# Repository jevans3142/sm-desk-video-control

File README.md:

# ADC Theatre - SM Desk Video Switcher

This repository hosts the hardware (in the form of KiCad schematics and PCB layouts) and 
firmware (in the form of C code) of the [ADC Theatre's](https://www.adctheatre.com) Stage 
Manager's Desk Video Switcher. This is a control panel within the SM desk on stage which 
provides remote control of a Blackmagic Design Videohub SDI switcher via Ethernet.

## Features
* Controls four screen outputs on the SM Desk, with six sources (which can differ for each of the screens) routable via 24 buttons on the desk
* Provides a special 'Show Relay' source which is switched between the Main and IR camera both on the SM Desk and around the building
* Is the interface for the Main/IR switch button the SM Desk, and also controls the mains contactor to activate the IR floodlights when in IR camera mode

## Configuration

Although some things such as number of buttons etc are fixed in hardware, some aspects can be customised via a text file 
on a microSD card read at boot. This provides the ADC with the ability to reconfigure for example which sources are availible on the SM desk without having to recompile firmware (as long as the physical buttons are relabeled of course!)

Items which can be configured: 
* Which router inputs are used as sources for each of the destinations 
* For the special 'Show Relay' source, which router inputs are the Main and IR camera 
* Which router outputs are used as 'Show Relay' outputs and should be automatically switched between Main and IR cameras in sync with the SM Desk
* IP address of the router

## Compilation
The microcontroller used is an ESP32 on an Olimex ESP32-PoE-ISO board. After standard installation of the esp-idf FreeRTOS toolchain, currently building on v5.1.1 as a stable version with the configuration included in the src folder (ie. when building do not run the idf.py set-target esp32 command as directed in the esp-idf Getting Started instructions to set up the default build config - just go straight to idf.py build)

## Hardware

There are two types of PCB required. Four 'switch-module' PCBs sit behind the four sets of buttons on the SM desk (four 
destinations with six sources each). One 'main-board' PCB is connected to these panel boards via ribbon cables, and also 
to Ethernet and power.

## Copyright
Copyright (c) 2021-2022 John Evans and contributors.
The ADC SM Desk Video Switcher hardware and firmware is released under Version 3 of the GNU General Public License.
See the LICENSE file for full details.

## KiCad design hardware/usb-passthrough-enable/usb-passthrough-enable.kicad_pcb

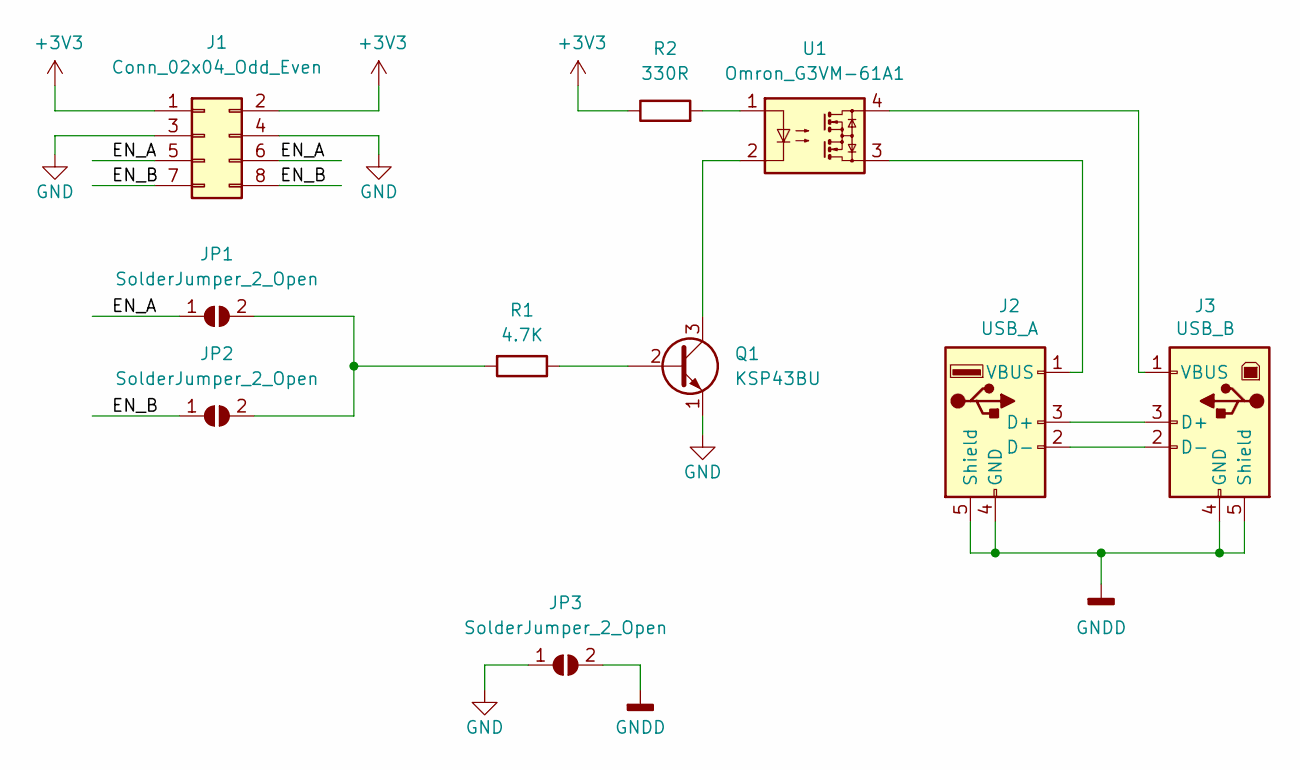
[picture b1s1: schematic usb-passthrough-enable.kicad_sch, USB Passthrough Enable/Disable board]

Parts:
J1: Conn_02x04_Odd_Even; PinHeader_2x04_P2.54mm_Vertical
J2: USB_A; USB_A_ASSMANN_A-USB-E-R
J3: USB_B; USB_B_ASSMANN_A-USBSB
JP1, JP2, JP3: SolderJumper_2_Open; SolderJumper-2_P1.3mm_Open_RoundedPad1.0x1.5mm
Q1: KSP43BU; TO-92_Inline
R1: 4.7K; R_Axial_DIN0207_L6.3mm_D2.5mm_P10.16mm_Horizontal
R2: 330R; R_Axial_DIN0207_L6.3mm_D2.5mm_P10.16mm_Horizontal
U1: Omron_G3VM-61A1; DIP-4_W7.62mm

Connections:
+3V3: J1.1, J1.2, R2.1
/EN_A: J1.5, J1.6, JP1.1 (A)
/EN_B: J1.7, J1.8, JP2.1 (A)
GND: J1.3, J1.4, JP3.1 (A), Q1.1 (E)
GNDD: J2.4 (GND), J2.5 (Shield), J3.4 (GND), J3.5 (Shield), JP3.2 (B)
unnamed: J2.3 (D+), J3.3 (D+)
unnamed: J2.2 (D-), J3.2 (D-)
unnamed: J2.1 (VBUS), U1.3
unnamed: J3.1 (VBUS), U1.4
unnamed: JP1.2 (B), JP2.2 (B), R1.2
unnamed: Q1.2 (B), R1.1
unnamed: Q1.3 (C), U1.2
unnamed: R2.2, U1.1

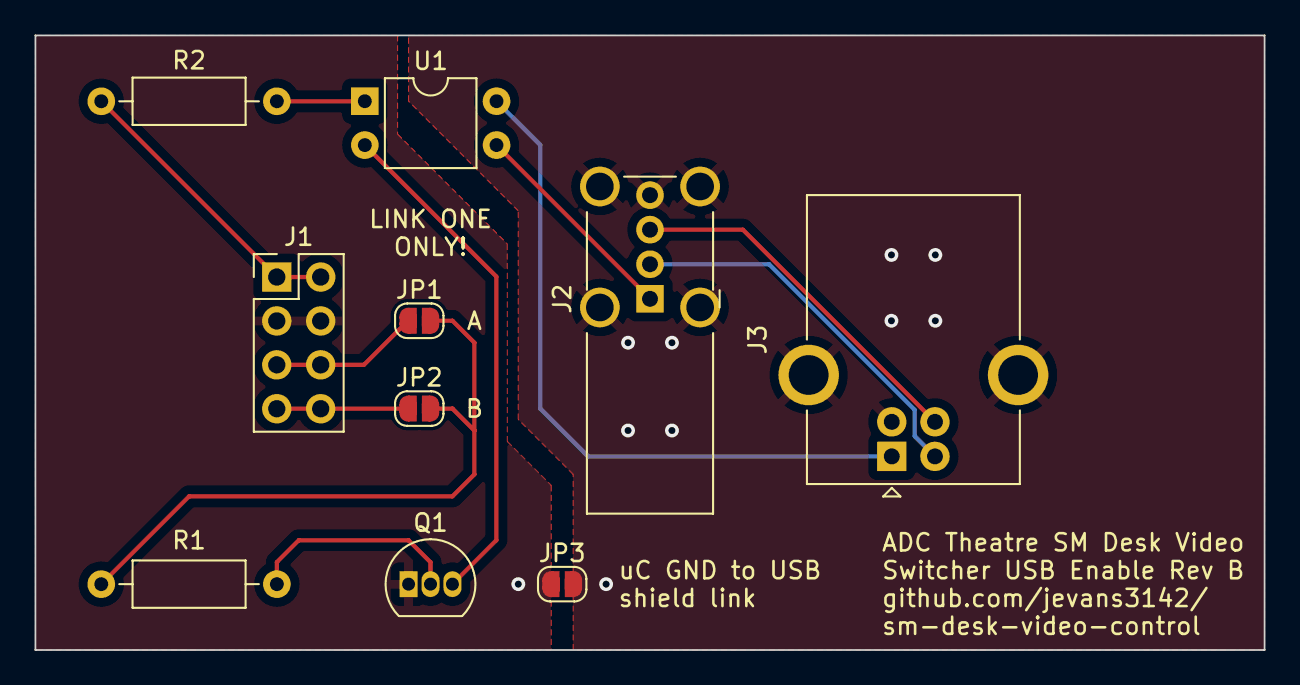
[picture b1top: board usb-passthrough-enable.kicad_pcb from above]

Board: 2 copper layers, 71.1 x 35.6 mm, 10 parts (0 on the bottom side), 13 nets.

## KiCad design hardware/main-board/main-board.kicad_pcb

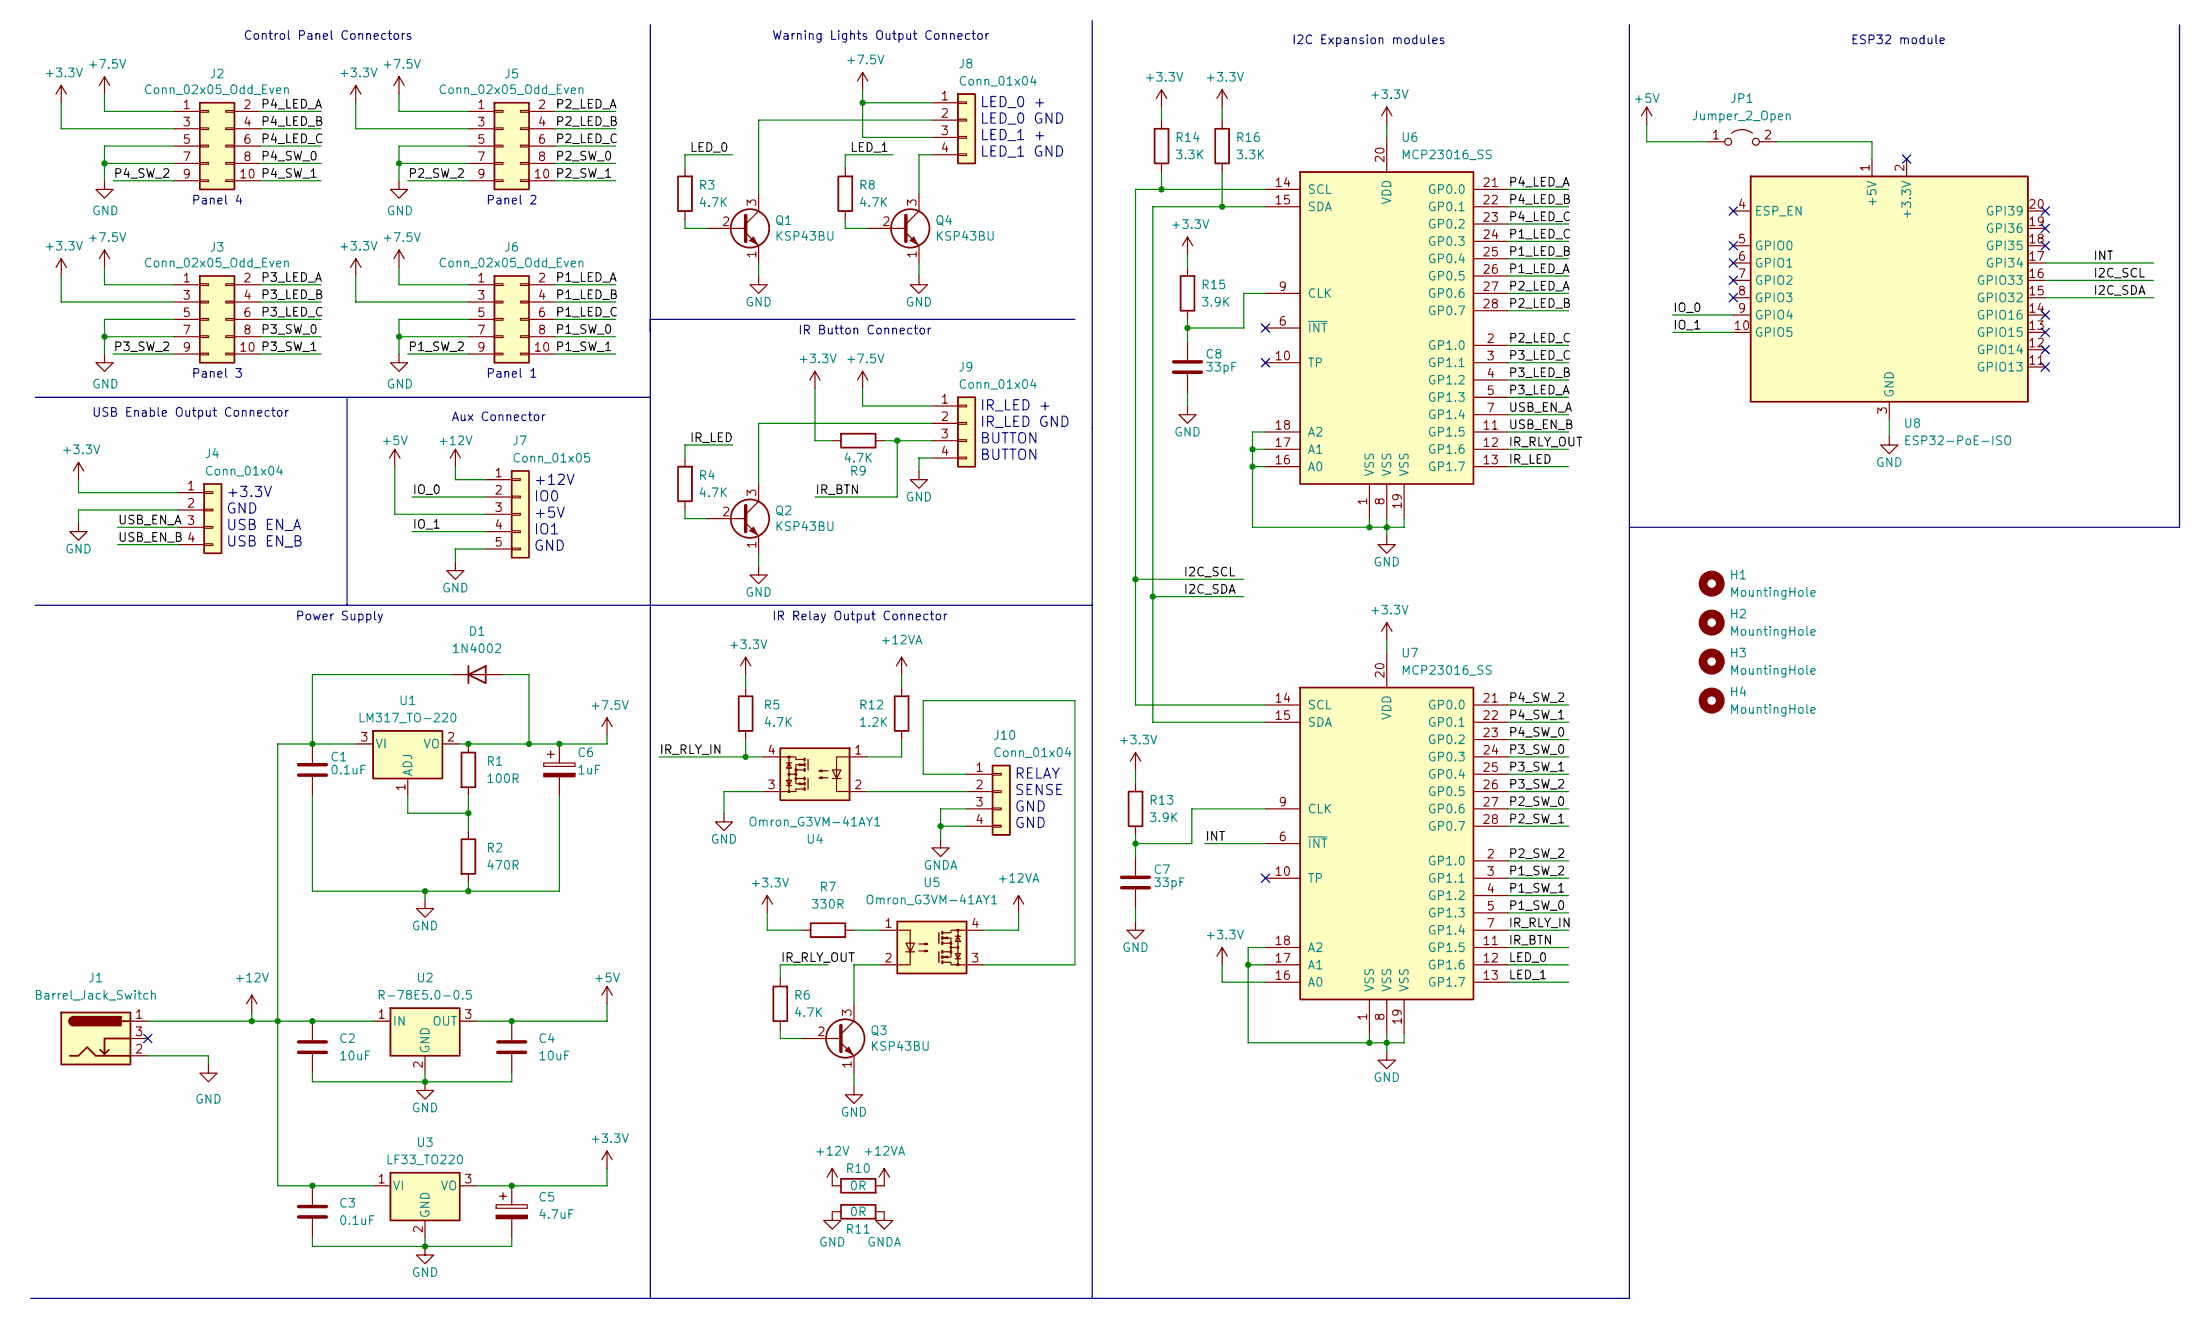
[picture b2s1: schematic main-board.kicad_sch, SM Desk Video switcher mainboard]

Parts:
C1, C3: 0.1uF; C_Disc_D4.7mm_W2.5mm_P5.00mm
C2, C4: 10uF; C_1210_3225Metric_Pad1.33x2.70mm_HandSolder
C5: 4.7uF; CP_Radial_D5.0mm_P2.00mm
C6: 1uF; CP_Radial_D5.0mm_P2.00mm
C7, C8: 33pF; C_Disc_D4.7mm_W2.5mm_P5.00mm
D1: 1N4002; D_DO-34_SOD68_P10.16mm_Horizontal
H1, H2, H3, H4: MountingHole; MountingHole_4.3mm_M4
J1: Barrel_Jack_Switch; BarrelJack_RS-PRO_12V1A_14.5mmL
J2, J3, J5, J6: Conn_02x05_Odd_Even; PinHeader_AWHW_2x05_P2.54mm_Vertical
J4, J8, J9, J10: Conn_01x04; PinHeader_1x04_P2.54mm_Vertical
J7: Conn_01x05; PinHeader_1x05_P2.54mm_Vertical
JP1: Jumper_2_Open; SolderJumper-2_P1.3mm_Open_TrianglePad1.0x1.5mm
Q1, Q2, Q3, Q4: KSP43BU; TO-92_Inline
R1: 100R; R_Axial_DIN0207_L6.3mm_D2.5mm_P10.16mm_Horizontal
R2: 470R; R_Axial_DIN0207_L6.3mm_D2.5mm_P10.16mm_Horizontal
R3, R4, R5, R6, R8, R9: 4.7K; R_Axial_DIN0207_L6.3mm_D2.5mm_P10.16mm_Horizontal
R7: 330R; R_Axial_DIN0207_L6.3mm_D2.5mm_P10.16mm_Horizontal
R10, R11: 0R; R_Axial_DIN0207_L6.3mm_D2.5mm_P10.16mm_Horizontal
R12: 1.2K; R_Axial_DIN0207_L6.3mm_D2.5mm_P10.16mm_Horizontal
R13, R15: 3.9K; R_Axial_DIN0207_L6.3mm_D2.5mm_P10.16mm_Horizontal
R14, R16: 3.3K; R_Axial_DIN0207_L6.3mm_D2.5mm_P10.16mm_Horizontal
U1: LM317_TO-220; TO-220-3_Horizontal_TabDown
U2: R-78E5.0-0.5; Converter_DCDC_RECOM_R-78E-0.5_THT
U3: LF33_TO220; TO-220-3_Horizontal_TabDown
U4, U5: Omron_G3VM-41AY1; DIP-4_W7.62mm
U6, U7: MCP23016_SS; DIP-28_W7.62mm
U8: ESP32-PoE-ISO; Olimex_ESP32_PoE_ISO

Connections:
+3V3: C5.1, J2.3, J3.3, J4.1, J5.3, J6.3, R5.1, R7.1, R9.2, R13.2, R14.2, R15.2, R16.2, U3.3 (VO), U6.20 (VDD), U7.16 (A0), U7.20 (VDD)
+5V: C4.1, J7.3, JP1.1 (A), U2.3 (OUT)
+7.5V: C6.1, D1.2 (A), J2.1, J3.1, J5.1, J6.1, J8.1, J8.3, J9.1, R1.1, U1.2 (VO)
+12V: C1.1, C2.1, C3.1, D1.1 (K), J1.1, J7.1, R10.1, U1.3 (VI), U2.1 (IN), U3.1 (VI)
+12VA: R10.2, R12.2, U5.4
/I2C_SCL: R14.1, U6.14 (SCL), U7.14 (SCL), U8.16 (GPIO33)
/I2C_SDA: R16.1, U6.15 (SDA), U7.15 (SDA), U8.15 (GPIO32)
/INT: U7.6 (~INT), U8.17 (GPI34)
/IO_0: J7.2, U8.9 (GPIO4)
/IO_1: J7.4, U8.10 (GPIO5)
/IR_BTN: J9.3, R9.1, U7.11 (GP1.5)
/IR_LED: R4.2, U6.13 (GP1.7)
/IR_RLY_IN: R5.2, U4.4, U7.7 (GP1.4)
/IR_RLY_OUT: R6.2, U6.12 (GP1.6)
/LED_0: R3.2, U7.12 (GP1.6)
/LED_1: R8.2, U7.13 (GP1.7)
/P1_LED_A: J6.2, U6.26 (GP0.5)
/P1_LED_B: J6.4, U6.25 (GP0.4)
/P1_LED_C: J6.6, U6.24 (GP0.3)
/P1_SW_0: J6.8, U7.5 (GP1.3)
/P1_SW_1: J6.10, U7.4 (GP1.2)
/P1_SW_2: J6.9, U7.3 (GP1.1)
/P2_LED_A: J5.2, U6.27 (GP0.6)
/P2_LED_B: J5.4, U6.28 (GP0.7)
/P2_LED_C: J5.6, U6.2 (GP1.0)
/P2_SW_0: J5.8, U7.27 (GP0.6)
/P2_SW_1: J5.10, U7.28 (GP0.7)
/P2_SW_2: J5.9, U7.2 (GP1.0)
/P3_LED_A: J3.2, U6.5 (GP1.3)
/P3_LED_B: J3.4, U6.4 (GP1.2)
/P3_LED_C: J3.6, U6.3 (GP1.1)
/P3_SW_0: J3.8, U7.24 (GP0.3)
/P3_SW_1: J3.10, U7.25 (GP0.4)
/P3_SW_2: J3.9, U7.26 (GP0.5)
/P4_LED_A: J2.2, U6.21 (GP0.0)
/P4_LED_B: J2.4, U6.22 (GP0.1)
/P4_LED_C: J2.6, U6.23 (GP0.2)
/P4_SW_0: J2.8, U7.23 (GP0.2)
/P4_SW_1: J2.10, U7.22 (GP0.1)
/P4_SW_2: J2.9, U7.21 (GP0.0)
/USB_EN_A: J4.3, U6.7 (GP1.4)
/USB_EN_B: J4.4, U6.11 (GP1.5)
GND: C1.2, C2.2, C3.2, C4.2, C5.2, C6.2, C7.2, C8.2, J1.2, J2.5, J2.7, J3.5, J3.7, J4.2, J5.5, J5.7, J6.5, J6.7, J7.5, J9.4, Q1.1 (E), Q2.1 (E), Q3.1 (E), Q4.1 (E), R2.2, R11.1, U2.2 (GND), U3.2 (GND), U4.3, U6.1 (VSS), U6.8 (VSS), U6.16 (A0), U6.17 (A1), U6.18 (A2), U6.19 (VSS), U7.1 (VSS), U7.8 (VSS), U7.17 (A1), U7.18 (A2), U7.19 (VSS), U8.3 (GND)
GNDA: J10.3, J10.4, R11.2
unnamed: C7.1, R13.1, U7.9 (CLK)
unnamed: C8.1, R15.1, U6.9 (CLK)
unnamed: J8.2, Q1.3 (C)
unnamed: J8.4, Q4.3 (C)
unnamed: J9.2, Q2.3 (C)
unnamed: J10.1, U5.3
unnamed: J10.2, U4.2
unnamed: JP1.2 (B), U8.1 (+5V)
unnamed: Q1.2 (B), R3.1
unnamed: Q2.2 (B), R4.1
unnamed: Q3.2 (B), R6.1
unnamed: Q3.3 (C), U5.2
unnamed: Q4.2 (B), R8.1
unnamed: R1.2, R2.1, U1.1 (ADJ)
unnamed: R7.2, U5.1
unnamed: R12.1, U4.1

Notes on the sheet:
+3.3V GND USB EN_A USB EN_B
IR Button Connector
Power Supply
Panel 2
Panel 4
Aux Connector
RELAY SENSE GND GND
Warning Lights Output Connector
Panel 1
USB Enable Output Connector
LED_0 + LED_0 GND LED_1 + LED_1 GND
+12V IO0 +5V IO1 GND
Panel 3
I2C Expansion modules
ESP32 module
IR_LED + IR_LED GND BUTTON BUTTON
IR Relay Output Connector
Control Panel Connectors

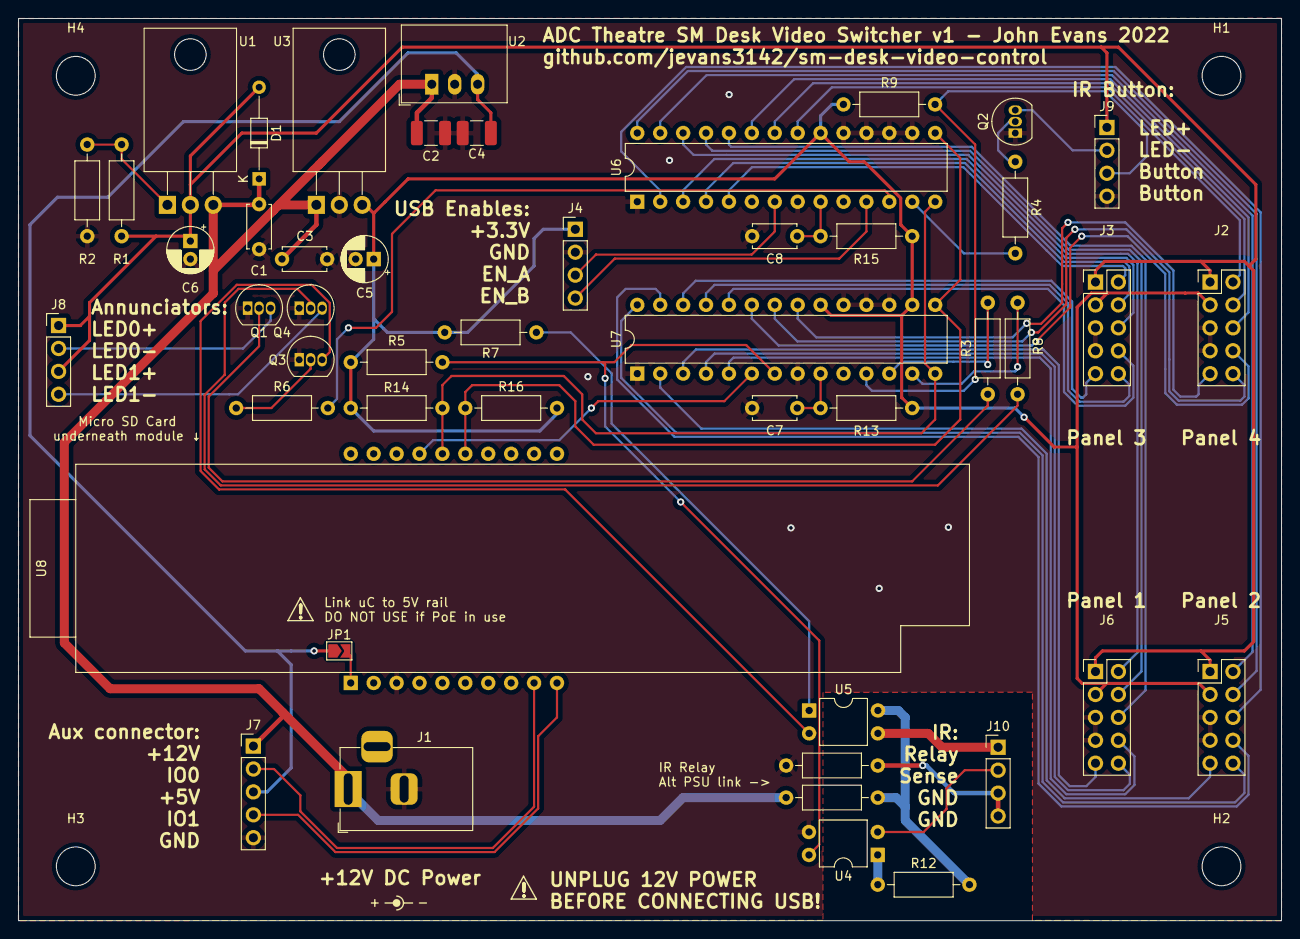
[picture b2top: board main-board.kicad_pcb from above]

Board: 2 copper layers, 140.0 x 100.0 mm, 52 parts (0 on the bottom side), 60 nets.

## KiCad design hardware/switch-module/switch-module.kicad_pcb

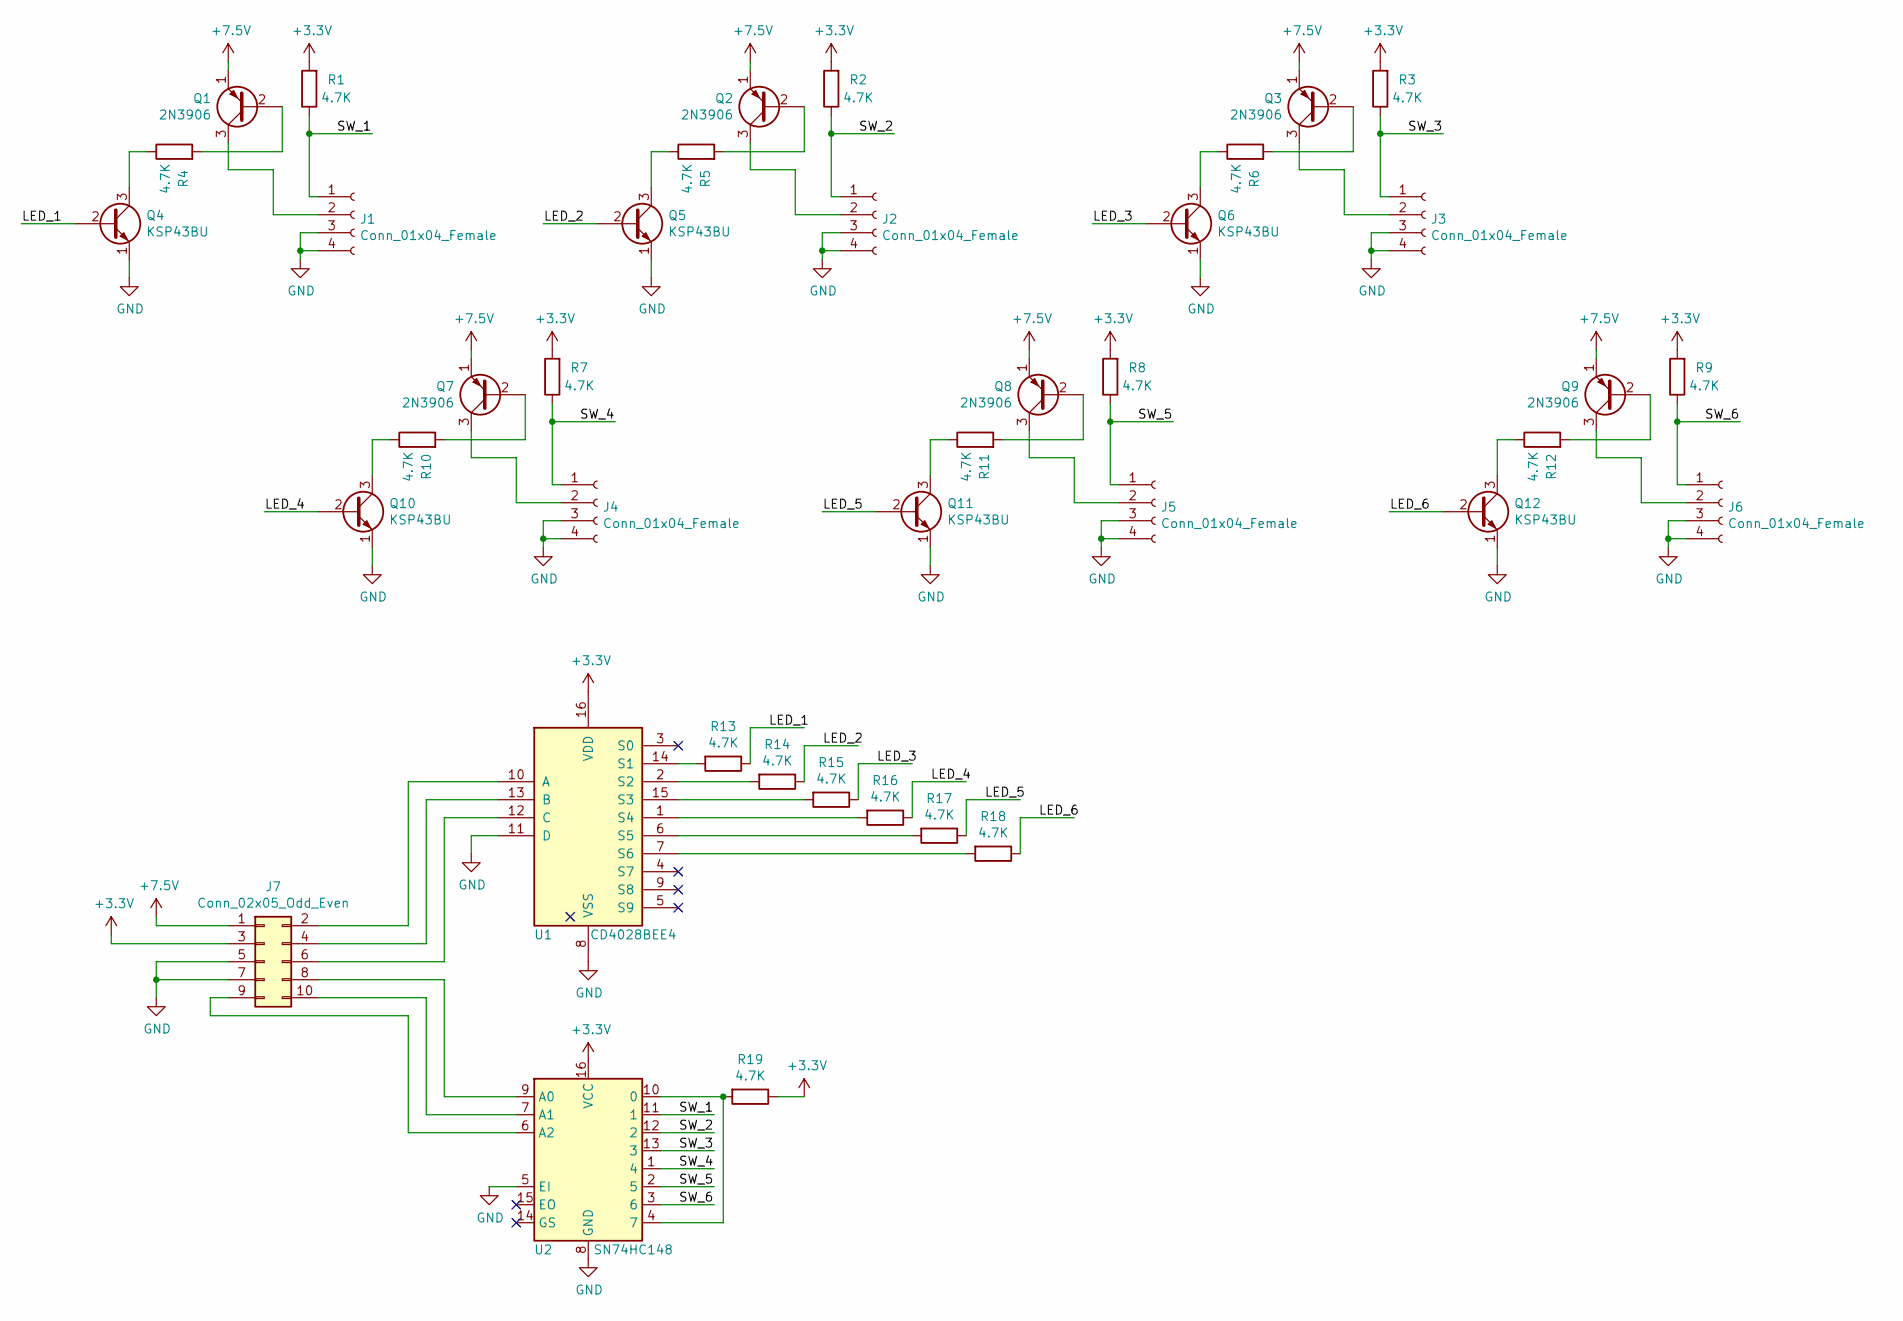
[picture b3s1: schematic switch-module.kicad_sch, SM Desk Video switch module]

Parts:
J1, J2, J3, J4, J5, J6: Conn_01x04_Female; PinHeader_1x04_P2.54mm_Vertical
J7: Conn_02x05_Odd_Even; PinHeader_AWHW_2x05_P2.54mm_Vertical
Q1, Q2, Q3, Q7, Q8, Q9: 2N3906; TO-92_Inline
Q4, Q5, Q6, Q10, Q11, Q12: KSP43BU; TO-92_Inline
R1, R2, R3, R4, R5, R6, R7, R8, R9, R10, R11, R12, R13, R14, R15, R16, R17, R18, R19: 4.7K; R_Axial_DIN0207_L6.3mm_D2.5mm_P10.16mm_Horizontal
U1: CD4028BEE4; DIP-16_W7.62mm_Socket
U2: SN74HC148; DIP-16_W7.62mm_Socket

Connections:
+3V3: J7.3, R1.2, R2.2, R3.2, R7.2, R8.2, R9.2, R19.1, U1.16 (VDD), U2.16 (VCC)
+7.5V: J7.1, Q1.1 (E), Q2.1 (E), Q3.1 (E), Q7.1 (E), Q8.1 (E), Q9.1 (E)
/LED_1: Q4.2 (B), R13.1
/LED_2: Q5.2 (B), R14.1
/LED_3: Q6.2 (B), R15.1
/LED_4: Q10.2 (B), R16.1
/LED_5: Q11.2 (B), R17.1
/LED_6: Q12.2 (B), R18.1
/SW_1: J1.1, R1.1, U2.11 (1)
/SW_2: J2.1, R2.1, U2.12 (2)
/SW_3: J3.1, R3.1, U2.13 (3)
/SW_4: J4.1, R7.1, U2.1 (4)
/SW_5: J5.1, R8.1, U2.2 (5)
/SW_6: J6.1, R9.1, U2.3 (6)
GND: J1.3, J1.4, J2.3, J2.4, J3.3, J3.4, J4.3, J4.4, J5.3, J5.4, J6.3, J6.4, J7.5, J7.7, Q4.1 (E), Q5.1 (E), Q6.1 (E), Q10.1 (E), Q11.1 (E), Q12.1 (E), U1.8 (VSS), U1.11 (D), U2.5 (EI), U2.8 (GND)
unnamed: J1.2, Q1.3 (C)
unnamed: J2.2, Q2.3 (C)
unnamed: J3.2, Q3.3 (C)
unnamed: J4.2, Q7.3 (C)
unnamed: J5.2, Q8.3 (C)
unnamed: J6.2, Q9.3 (C)
unnamed: J7.2, U1.10 (A)
unnamed: J7.4, U1.13 (B)
unnamed: J7.6, U1.12 (C)
unnamed: J7.8, U2.9 (A0)
unnamed: J7.9, U2.6 (A2)
unnamed: J7.10, U2.7 (A1)
unnamed: Q1.2 (B), R4.2
unnamed: Q2.2 (B), R5.2
unnamed: Q3.2 (B), R6.2
unnamed: Q4.3 (C), R4.1
unnamed: Q5.3 (C), R5.1
unnamed: Q6.3 (C), R6.1
unnamed: Q7.2 (B), R10.2
unnamed: Q8.2 (B), R11.2
unnamed: Q9.2 (B), R12.2
unnamed: Q10.3 (C), R10.1
unnamed: Q11.3 (C), R11.1
unnamed: Q12.3 (C), R12.1
unnamed: R13.2, U1.14 (S1)
unnamed: R14.2, U1.2 (S2)
unnamed: R15.2, U1.15 (S3)
unnamed: R16.2, U1.1 (S4)
unnamed: R17.2, U1.6 (S5)
unnamed: R18.2, U1.7 (S6)
unnamed: R19.2, U2.4 (7), U2.10 (0)

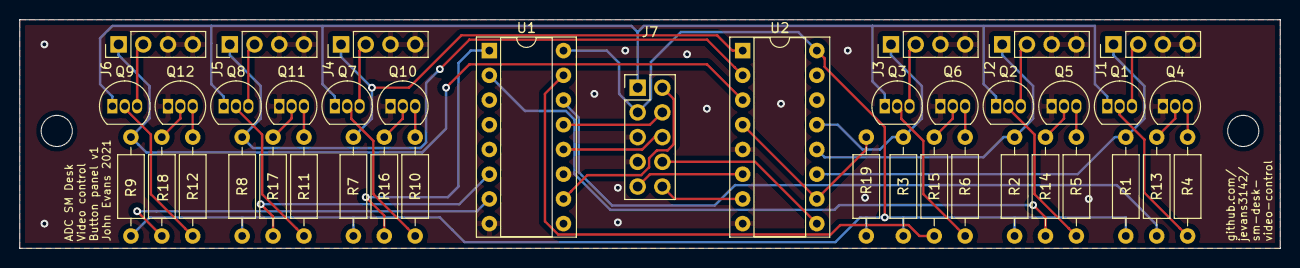
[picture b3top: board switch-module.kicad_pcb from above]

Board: 2 copper layers, 129.5 x 23.5 mm, 40 parts (0 on the bottom side), 46 nets.

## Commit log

2021-09-19 Add switch module PCB design
    v1 design for PCB that sits behind a module of 6 buttons and encodes/decodes into 3 bit format to connect to microcontroller. Also provides transistors for driving LEDs at a higher voltage than logic.
2021-10-17 Software initial commit
    .ino and .h file for software
2021-10-17 Interface to button panels
    Add basic interface to button panels and LEDs; debouncing to be added later
2021-10-18 Add gitattributes file
    Identify header files correctly
2021-10-18 Update Readme
    Add info on how to compile
2021-10-24 Correct buttons code
    After hardware testing switch panel, correct logic errors in buttons read code
2021-10-24 Improved readme text
2021-10-24 Begin serial software
    Alternate version for connection to existing RS232 based VGA switcher if required
2021-10-24 Serial switcher interface
    Basic code to control serial switcher; brings into line with old version of switcher
2021-10-24 Basic connection to switcher
    Add structure to main loop to maintain a connection to the videohub over Ethernet
2021-10-25 Add functions for IR button and warning lights
    Basic functions for IR button, IR relay and ethernet fail warning lights
2021-10-25 Add DHCP lease renew
    Command in main loop to tell arduino to keep our lease live
2022-01-16 Updates to PCB layouts
2022-01-29 Update README with new Teensyduino version
2022-02-03 Change control panel pins
    to avoid inbuilt devboard LED
2022-05-30 Update main-board PCB
    Update main board PCB to Kicad 6.0 as well as roughly complete PCB layout
2022-06-03 Complete main board schematic
2022-09-19 Switch microcontroller to ESP32
    Using Olimex ESP32-PoE-ISO board - initial software commit, PCB still to modify
2022-09-29 Start local IO interface code
    Initial commit of structure of IO for local control panel
2022-10-10 Basic I2C funcs
    Read/write to external modules
2022-10-15 PCB updates
    Alter schematic to use ESP32 and add final PCB for USB enable/disables
2022-11-20 Rev A mainboard PCB
    Altered to split IR relay off into isolated section
2022-12-25 Complete basic local IO code
    Rough draft of I2C interfacing and so on; some funcs incomplete in particular response to board power on/off - some level of debouncing and using interrupts rather than polling still todo.
2023-01-15 Restructure IO; debouncing and input event queue
    Add proper debouncing polling, sends events back to main file to process input logic. Also separates input and output buffers/mutexes
2023-03-12 Tidy up local IO module
    Minor formatting etc mods
2023-03-14 Input message queue system improvements
    Change to more flexible message passing system using structs rather than bare ints
2023-03-26 Add settings load from SD card
    Add module which loads and parses config file from SD card, description of config file format
2023-03-26 Basic ethernet module, command send logic
    Add socket based ethernet logic that will handle sending of commands from the input logic. Should robustly(ish?) handle being unplugged/replugged etc from ethernet cable, router being power cycled et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
2023-04-02 Add processing of incoming video routing confirm messages
    Add basic TCP text message receive loop and add to main logic to switch button LEDs when required. Corrected some off by one errors.
2023-04-15 Set correct MAC and default router IP
2023-04-15 Ignore KiCad backup files in gitgnore
2023-04-16 Add vegas mode
    Hold down leftmost two source buttons on SM desk panel during boot to enter a test mode for buttons and LEDs
2023-04-16 Fix off-by-one error in SD card load
    Values were not being converted from router 1-40 to variable 0-39
2023-04-16 IR logic/coping with SM Desk reset
    All logic for switching IR and coping with PSU up/down
2023-04-17 Update sample config file
    To be in line with current setup
2023-05-02 Fix vegas mode
    Was broken by fix for SM desk PSU restart, was trying to trigger ethernet commands that weren't there
2023-05-02 Properly fix vegas mode
    Honestly, this time...
2023-06-04 Like, really, really fix vegas mode
    Tested at ADC unit and needed extra delay to work...
2023-06-04 Fix ethernet/TCP timeout bug
    Add timeouts to reset connection
2023-10-15 Update to ESP v5.1.1
    Includes fix for mistake in code exposed by GCC upgrade - static variables weren't correctly marked
2023-10-15 Update .gitignore
    To exclude VS code files
2023-10-19 Update README
    for new ESP version - forgot to update...
2024-06-15 Fix not powering on Ethernet PHY
    Wasn't properly changed as part of ESP 5.1.1 update
2024-06-15 USB switching
    Add initial support for USB switching depending on screen viewed
2024-06-29 Add logging for USB switching, update default file
2024-06-29 Fix partial block issue with TCP stack
2024-07-08 Rev B USB switching PCB
    Correct error in ground plane
2024-08-17 Update Main/IR config to current ADC setup in config file
